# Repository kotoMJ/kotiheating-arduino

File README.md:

# kotiheating-arduino

IoT KotiHeating project for remote heating control realized with Arduino HW.

## Functionality

KotiHeating offers 3 heating modes:
1) OFF - heating is set to non-freezing level (5°C)
2) MANUAL - allows set heating level from 18°C to 28°C
3) AUTOMATIC - reads temperature from locally saved matrix

## WiFi Connectivity

KotiHeating exposes following endpoints via WIFI:
- TBD.
- TBD.

## Internet Connectivity

Kotiheating is periodically connecting to server endpoint to update AUTOMATIC matrix 
and to save last known state of the device.

Server matrix can be changed on the server TBD.

Server expose last known state of the KotiHeating via API TBD.

### HTTPS connection

#### Cipher suite supported by device
Current solution is for chip ESP8266.
This chip supports TLS1.1 only and only in these two variants:
1)TLS_RSA_WITH_AES_256_CBC_SHA
2)TLS_RSA_WITH_AES_128_CBC_SHA

You can check your device running this program on it:
 `http.begin("https://www.howsmyssl.com/a/check", "4D 05 9F 78 25 B2 82 98 3A B9 4D 4D 41 71 FA D3 DF C4 65 B9");`

#### Cipher cuite supported by server
Then check which ciphers has been supported by server (kotopeky.cz in my case):
 
`nmap --script ssl-enum-ciphers -p 443 kotopeky.cz`
 
 If you find device's suite in the server's table, everything is ok.
 Otherwise you have to force server to support also device's cipher, or change device to fit server's cipher suite.
 
#### Key Fingerprint
 
If server's and device's cipher match. 
Then start connection using SHA1 fingerprint (look at the safari status bar for example).
In my case it's this:
 
 `http.begin("https://kotopeky.cz/api/kotinode/heating/status","63 FD D7 BB B4 A5 6C 00 57 0F 23 A2 FD 27 15 96 4A C2 4D 99");`

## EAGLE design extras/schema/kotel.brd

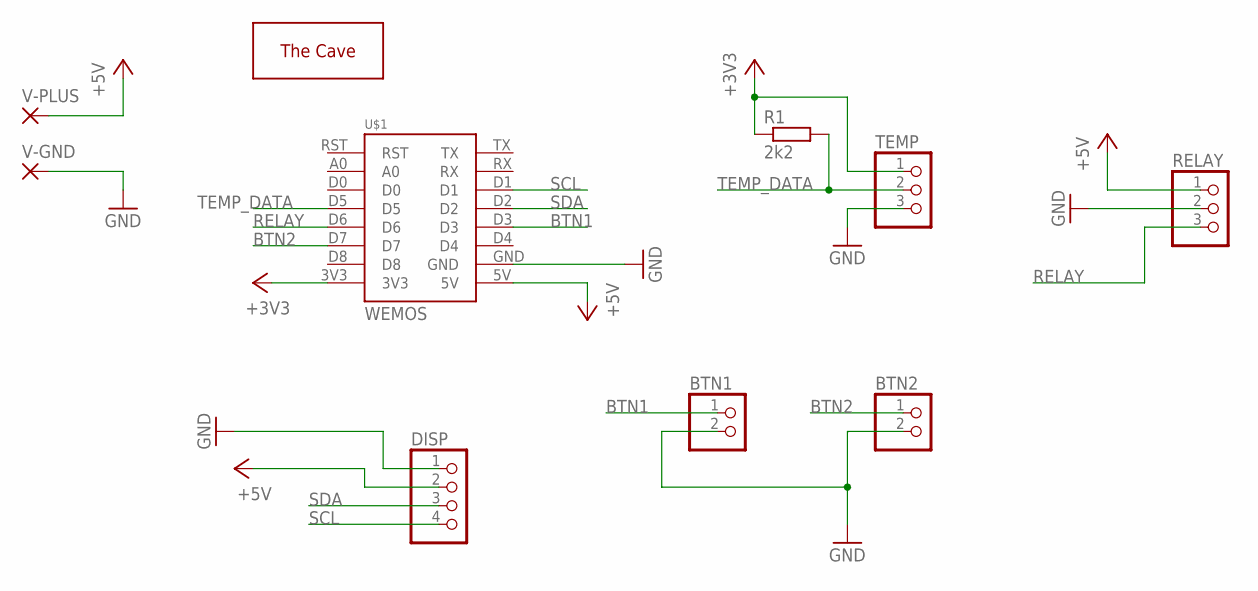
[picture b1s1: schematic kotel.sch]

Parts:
BTN1, BTN2: PINHD-1X2; 1X02
DISP: PINHD-1X4; 1X04
R1: 2k2; 0207/7
RELAY: PINHD-1X3; 1X03
TEMP: PINHD-1X3; 1X03
U$1: WEMOS
U$2: THECAVE_LOGO_COPPER_SMALL; LOGO_COPPER_SMALL
V-GND: WIREPAD2,54/0,9; 2,54/0,9
V-PLUS: WIREPAD2,54/0,9; 2,54/0,9

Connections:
+3V3: R1.1, TEMP.1, U$1.3V3
+5V: DISP.2, RELAY.1, U$1.5V, V-PLUS.1
BTN1: BTN1.1, U$1.D3
BTN2: BTN2.1, U$1.D7
GND: BTN1.2, BTN2.2, DISP.1, RELAY.2, TEMP.3, U$1.GND, V-GND.1
RELAY: RELAY.3, U$1.D6
SCL: DISP.4, U$1.D1
SDA: DISP.3, U$1.D2
TEMP_DATA: R1.2, TEMP.2, U$1.D5

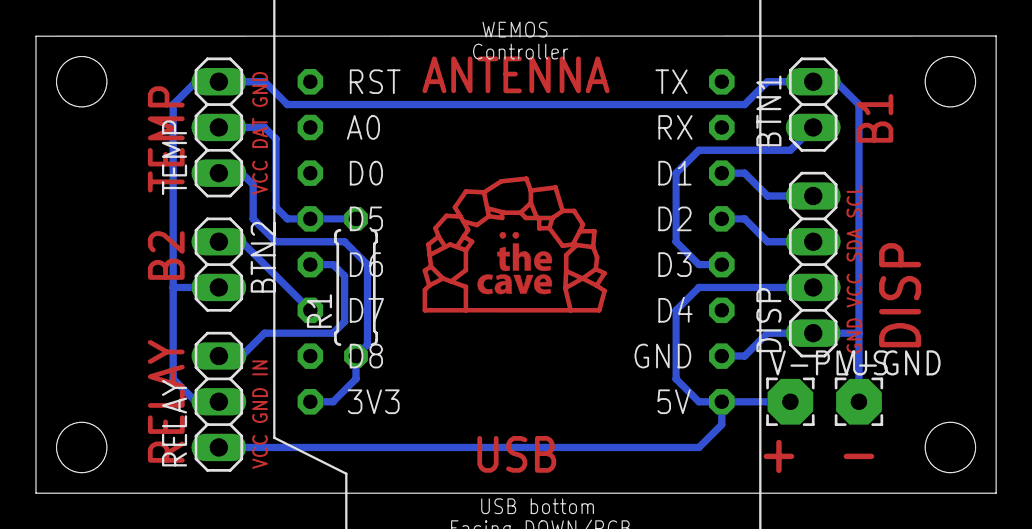
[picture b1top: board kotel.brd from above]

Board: 2 copper layers, 53.3 x 25.4 mm, 10 parts (0 on the bottom side), 9 nets.

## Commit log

2017-09-22 add howtos
2017-09-22 add required libraries
2017-09-22 Add firmware files
2017-10-02 Add heating schema
2017-10-03 Add eagle files
2017-10-17 Update project file according to conventions.
2017-10-17 Rename schema name according to project naming.
2017-10-17 Add HW photos.
2017-10-17 Update readme.
2017-10-17 Add skeleton for http client.
2017-10-22 Add basic logic for the client module.
2017-10-22 Fix client to fully communicate with the server in both sides.
2017-10-23 Update server endpoint. Increase server request to every 10 minutes.
2017-10-23 Attempt to fix failing SSH connection.
2017-11-13 Add crucial information about SSH connectivity.
2017-11-22 Update server communication.
2017-11-30 Change of the server's fingerprint.
2018-01-22 Update default time table.
2018-10-22 Adjust client.ino according to new API needs.
2018-11-13 Fix offset issue. Set offset of mid europe to be used in winter. Since winter is time to heat, it's more proper solution so far.
2018-11-21 Adjust request for writing device's status to server.
2018-12-03 Fix saturday shortcut.
2019-01-30 Add ability to force mode getting from the server.
2019-02-02 Adjust timer.
